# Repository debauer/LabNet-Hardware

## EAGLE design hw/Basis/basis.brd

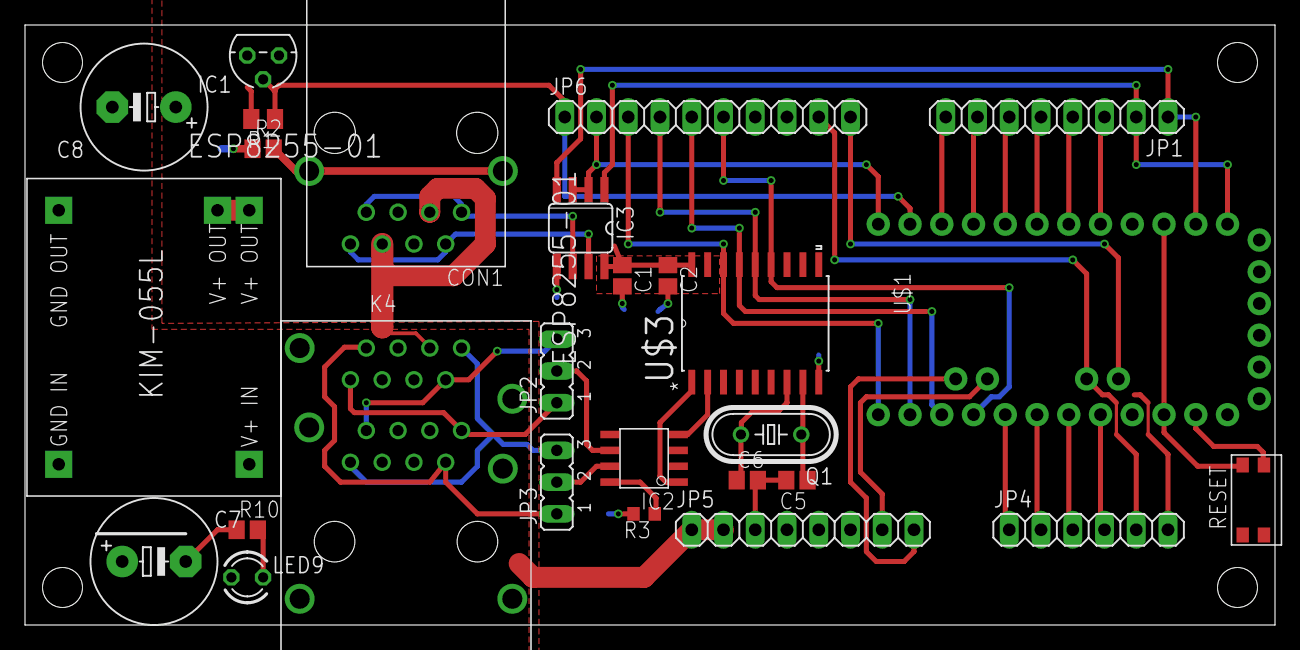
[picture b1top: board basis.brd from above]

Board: 2 copper layers, 100.0 x 48.0 mm, 27 parts (0 on the bottom side), 41 nets.

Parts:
C1, C2, C5, C6: C0805
C7, C8: E5-10,5
CON1: MEBP
IC1: DS1820TO92; TO-92
IC2: MCP2551; SO-8
IC3: MAX481CSA; SO08
JP1, JP5: 1X08
JP2, JP3: JP2
JP4: 1X06
JP6: 1X10
K4: 615016240521
LED9: LED3MM
MOD1: KIM-055L
Q1: HC49/S
R1: M0805
R2, R10: R0805
R3: 10k; R0603
RESET: 434351045816
U$1: ARDUINO_PRO_MINI
U$3: MCP2515-I/SO; SOIC127P1034X264-18N

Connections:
A0: JP4.1, U$1.17
A1: JP4.2, U$1.18
A2: JP4.3, U$1.19
A3_V24: JP4.4, U$1.20
A4_SDA: JP4.5, JP6.9, U$1.A4
A5_SCL: JP6.10, U$1.A5
A6: JP5.8, U$1.A6
A7: JP5.7, U$1.A7
CANH: IC2.7, JP3.2
CANH1: JP3.3, K4.A1, K4.B1
CANH2: JP3.1, K4.A7, K4.B7
CANL: IC2.6, JP2.2
CANL1: JP2.3, K4.A2, K4.B2
CANL2: JP2.1, K4.A8, K4.B8
CANRX: IC2.4, U$3.2
CANTX: IC2.1, U$3.1
D2: JP1.3, U$1.5
D3: JP1.4, U$1.6
D4: JP1.5, U$1.7
D5: JP1.6, U$1.8
D6: JP1.7, U$1.9
D7: JP1.8, U$1.10
D8: IC1.2, JP6.1, R1.1, U$1.11
D9: IC3.2, IC3.3, JP6.2, U$1.12
D10_SS: JP6.3, U$1.13, U$3.16
D11_MOSI: JP6.4, U$1.14, U$3.14
D12_MISO: JP6.5, U$1.15, U$3.15
D13_SCK: JP6.6, U$1.16, U$3.13
GND: C1.2, C2.2, C5.2, C6.2, C7.-, C8.-, CON1.4, CON1.5, IC1.1, IC3.5, JP5.3, JP5.4, JP6.7, K4.A4, K4.A5, K4.B4, K4.B5, MOD1.GNDIN, MOD1.GNDOUT, R2.1, R3.2, R10.1, RESET.2, U$1.4, U$1.23, U$3.9
MCP_OSC1: C5.1, Q1.1, U$3.8
MCP_OSC2: C6.1, Q1.2, U$3.7
unnamed: IC2.8, R3.1
unnamed: CON1.T1, CON1.T2, R2.2
unnamed: LED9.K, R10.2
P5V: C1.1, C2.1, C8.+, IC1.3, IC3.8, JP5.5, JP5.6, MOD1.V+OUT1, MOD1.V+OUT2, R1.2, U$1.21, U$3.18
P24P: C7.+, CON1.3, CON1.6, JP5.1, JP5.2, K4.A3, K4.A6, K4.B3, K4.B6, LED9.A, MOD1.V+IN
RESET: RESET.1, U$1.3, U$1.22
RS485_A: CON1.1, CON1.7, IC3.6
RS485_B: CON1.2, CON1.8, IC3.7
RX: IC3.4, JP1.1, U$1.2
TX: IC3.1, JP1.2, U$1.1

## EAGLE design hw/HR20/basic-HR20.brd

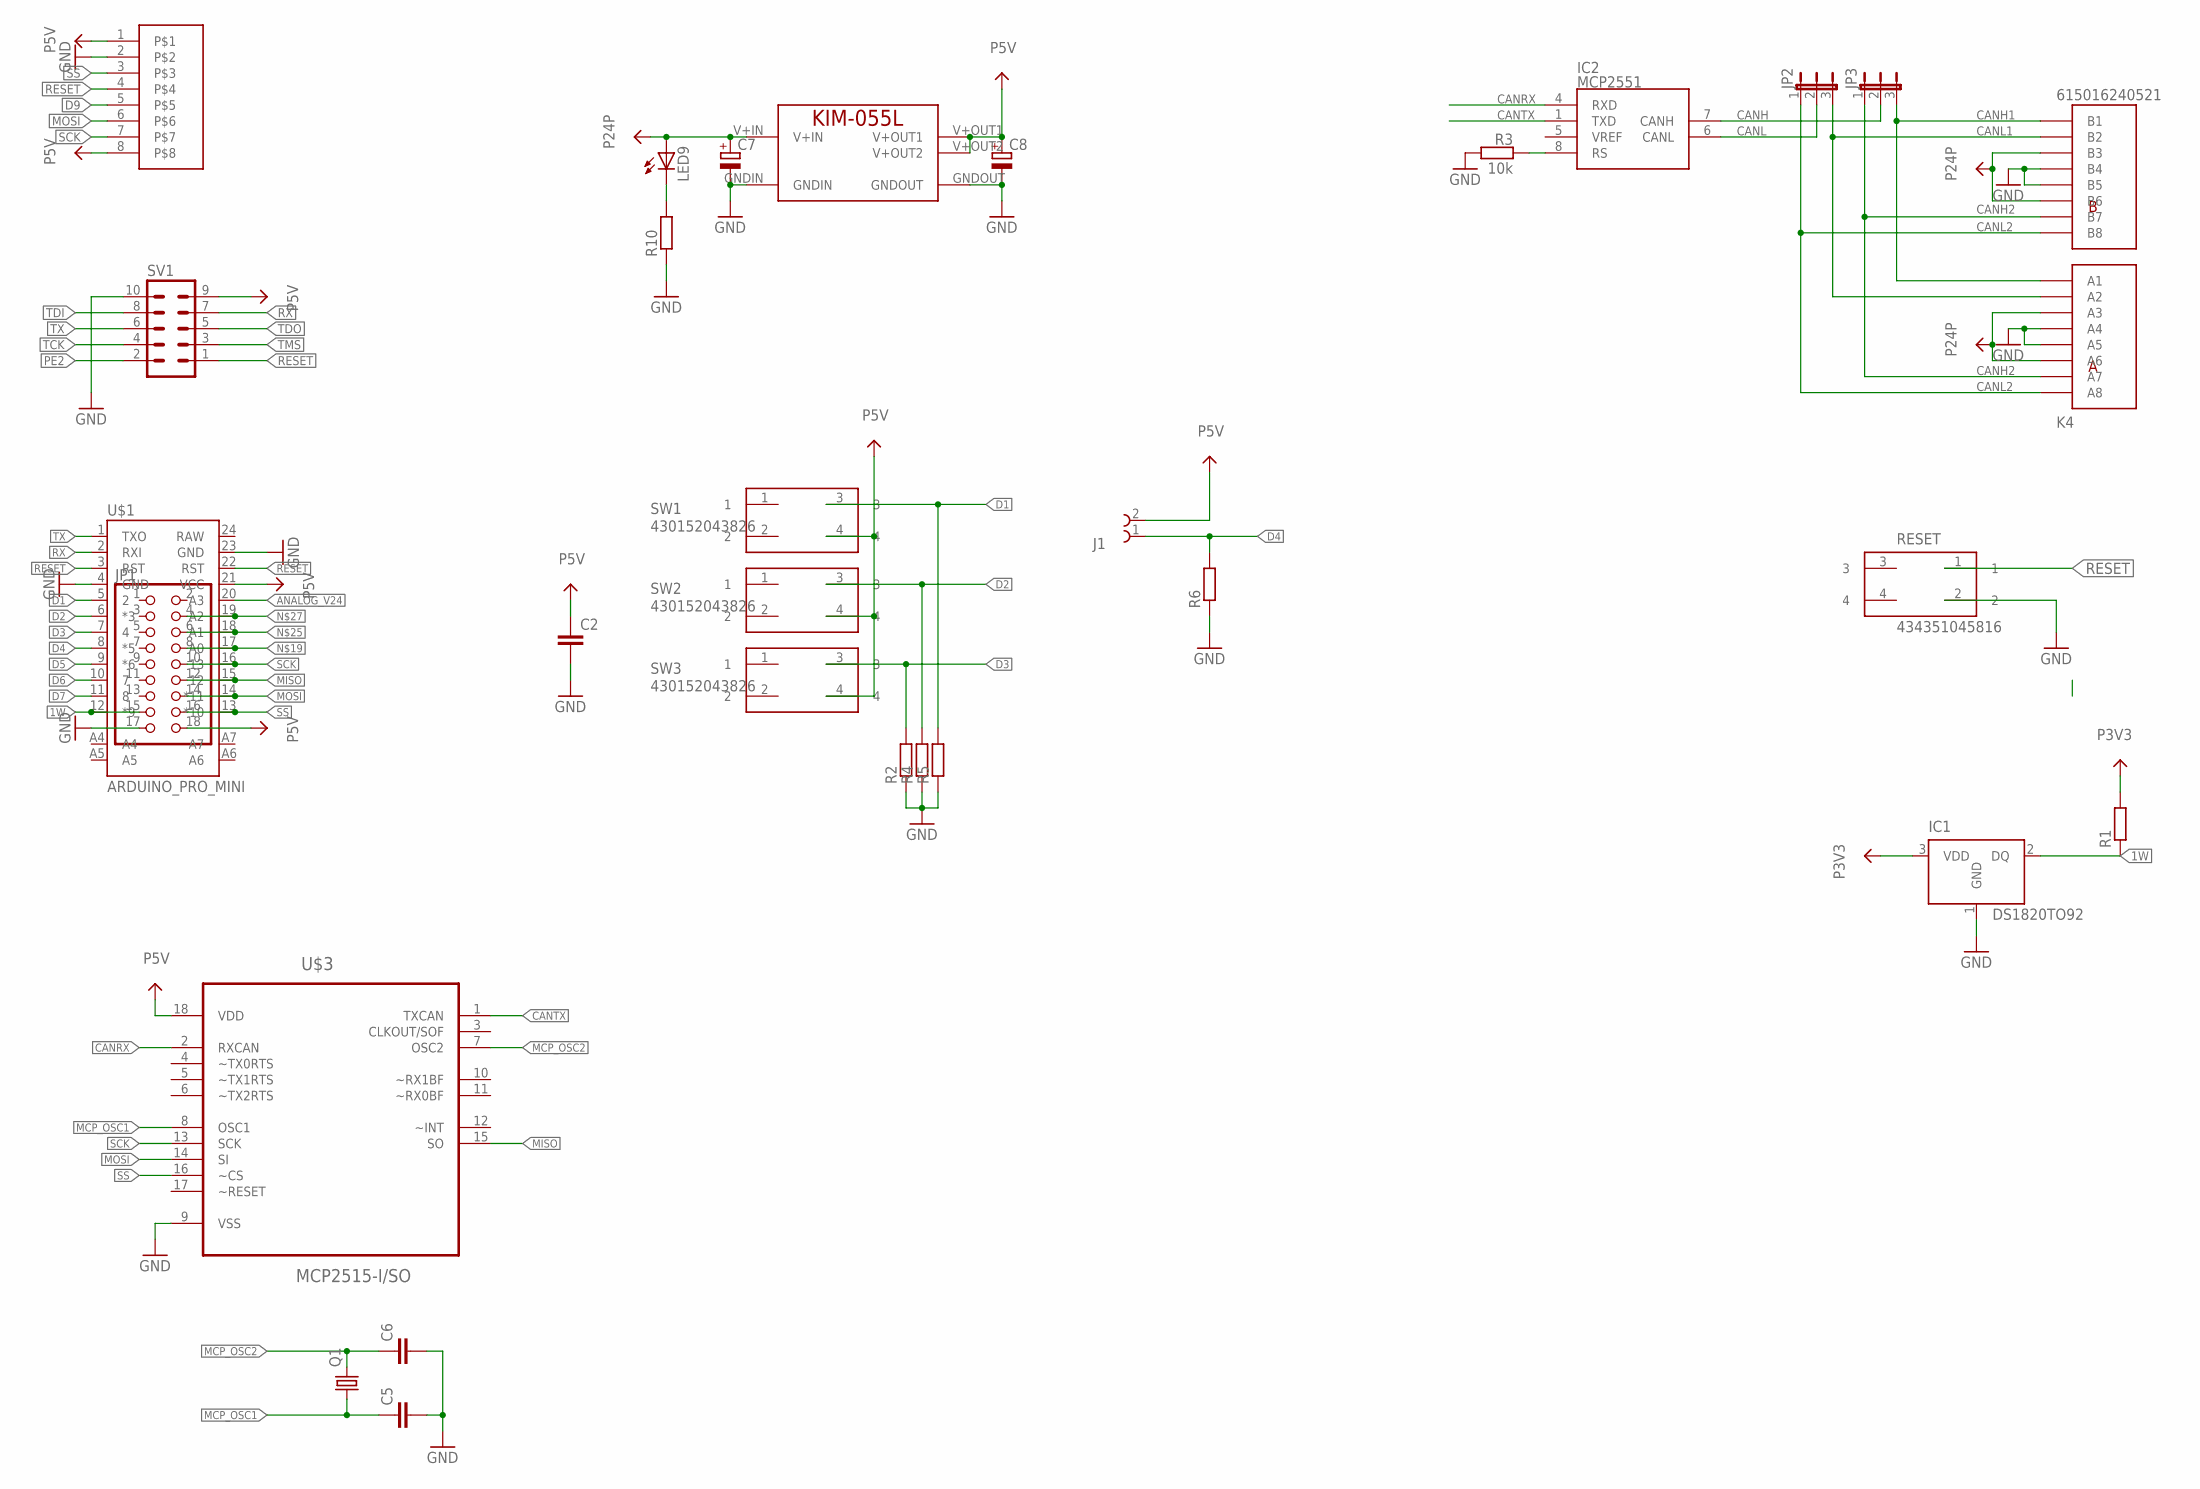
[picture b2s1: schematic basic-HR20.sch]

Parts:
C2, C5, C6: C-EUC0805; C0805
C7, C8: CPOL-EUE5-10.5; E5-10,5
IC1: DS1820TO92; TO-92
IC2: MCP2551; SO-8
J1: 691312510002
JP1: PINHD-2X9; 2X09
JP2, JP3: JP2E; JP2
K4: 615016240521
LED9: LED3MM
MOD1: KIM-055L
Q1: CRYSTALHC49S; HC49/S
R1: R-EU_M0805; M0805
R2, R4, R5, R6, R10: R-EU_R0805; R0805
R3: 10k; R0603
RESET: 434351045816
SV1: ML10
SW1, SW2, SW3: 430152043826
U$1: ARDUINO_PRO_MINI
U$2: 1.44-128X128
U$3: MCP2515-I/SO; SOIC127P1034X264-18N

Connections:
1W: IC1.2 (DQ), JP1.15, R1.1, U$1.12 (*9)
ANALOG_V24: U$1.20 (A3)
CANH: IC2.7 (CANH), JP3.2
CANH1: JP3.3, K4.A1, K4.B1
CANH2: JP3.1, K4.A7, K4.B7
CANL: IC2.6 (CANL), JP2.2
CANL1: JP2.3, K4.A2, K4.B2
CANL2: JP2.1, K4.A8, K4.B8
CANRX: IC2.4 (RXD), U$3.2 (RXCAN)
CANTX: IC2.1 (TXD), U$3.1 (TXCAN)
D1: R5.2, SW1.3, U$1.5 (2)
D2: R4.2, SW2.3, U$1.6 (*3)
D3: R2.2, SW3.3, U$1.7 (4)
D4: J1.1, R6.2, U$1.8 (*5)
D5: U$1.9 (*6)
D6: U$1.10 (7)
D7: U$1.11 (8)
D9: U$2.5
GND: C2.2, C5.2, C6.2, C7.-, C8.-, IC1.1 (GND), JP1.17, K4.A4, K4.A5, K4.B4, K4.B5, MOD1.GNDIN, MOD1.GNDOUT, R2.1, R3.2, R4.1, R5.1, R6.1, R10.1, RESET.2, SV1.10, U$1.4 (GND), U$1.23 (GND), U$2.2, U$3.9 (VSS)
MCP_OSC1: C5.1, Q1.1, U$3.8 (OSC1)
MCP_OSC2: C6.1, Q1.2, U$3.7 (OSC2)
MISO: JP1.12, U$1.15 (12), U$3.15 (SO)
MOSI: JP1.14, U$1.14 (*11), U$2.6, U$3.14 (SI)
unnamed: IC2.8 (RS), R3.1
unnamed: LED9.K (C), R10.2
unnamed: JP1.8, U$1.17 (A0)
unnamed: JP1.6, U$1.18 (A1)
unnamed: JP1.4, U$1.19 (A2)
P3V3: IC1.3 (VDD), R1.2
P5V: C2.1, C8.+, J1.2, JP1.18, MOD1.V+OUT1, MOD1.V+OUT2, SV1.9, SW1.4, SW2.4, SW3.4, U$1.21 (VCC), U$2.1, U$2.8, U$3.18 (VDD)
P24P: C7.+, K4.A3, K4.A6, K4.B3, K4.B6, LED9.A, MOD1.V+IN
PE2: SV1.2
RESET: RESET.1, SV1.1, U$1.3 (RST), U$1.22 (RST), U$2.4
RX: SV1.7, U$1.2 (RXI)
SCK: JP1.10, U$1.16 (13), U$2.7, U$3.13 (SCK)
SS: JP1.16, U$1.13 (*10), U$2.3, U$3.16 (~CS)
TCK: SV1.4
TDI: SV1.8
TDO: SV1.5
TMS: SV1.3
TX: SV1.6, U$1.1 (TXO)

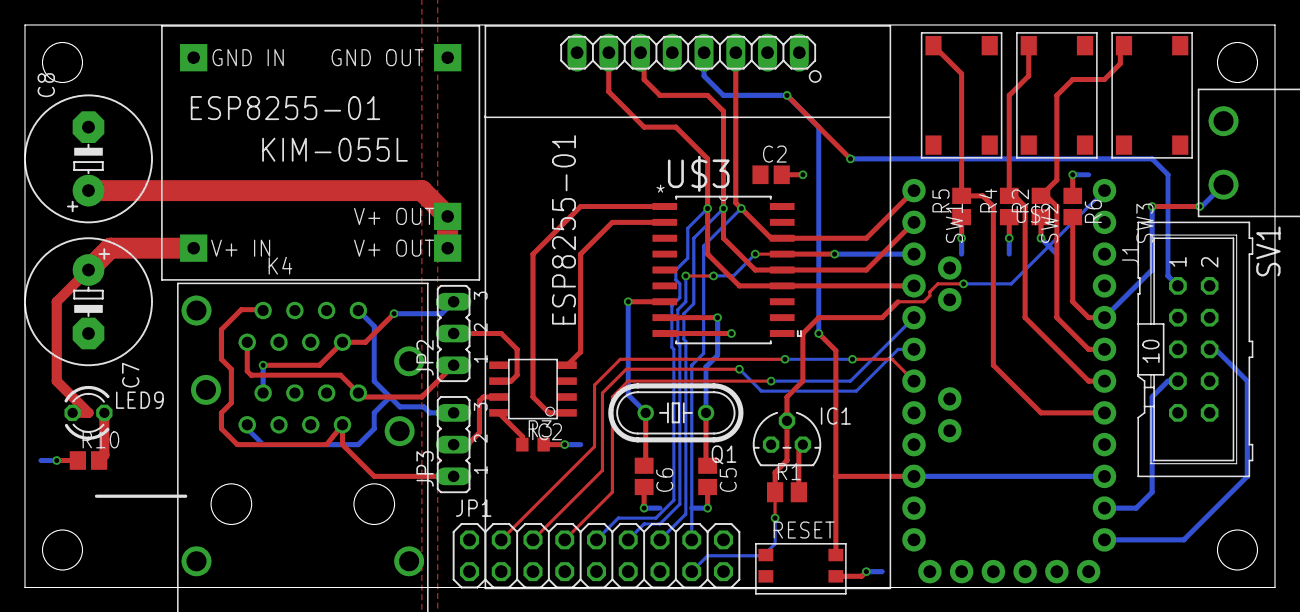
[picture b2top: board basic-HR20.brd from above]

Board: 2 copper layers, 100.0 x 45.0 mm, 30 parts (0 on the bottom side), 31 nets.

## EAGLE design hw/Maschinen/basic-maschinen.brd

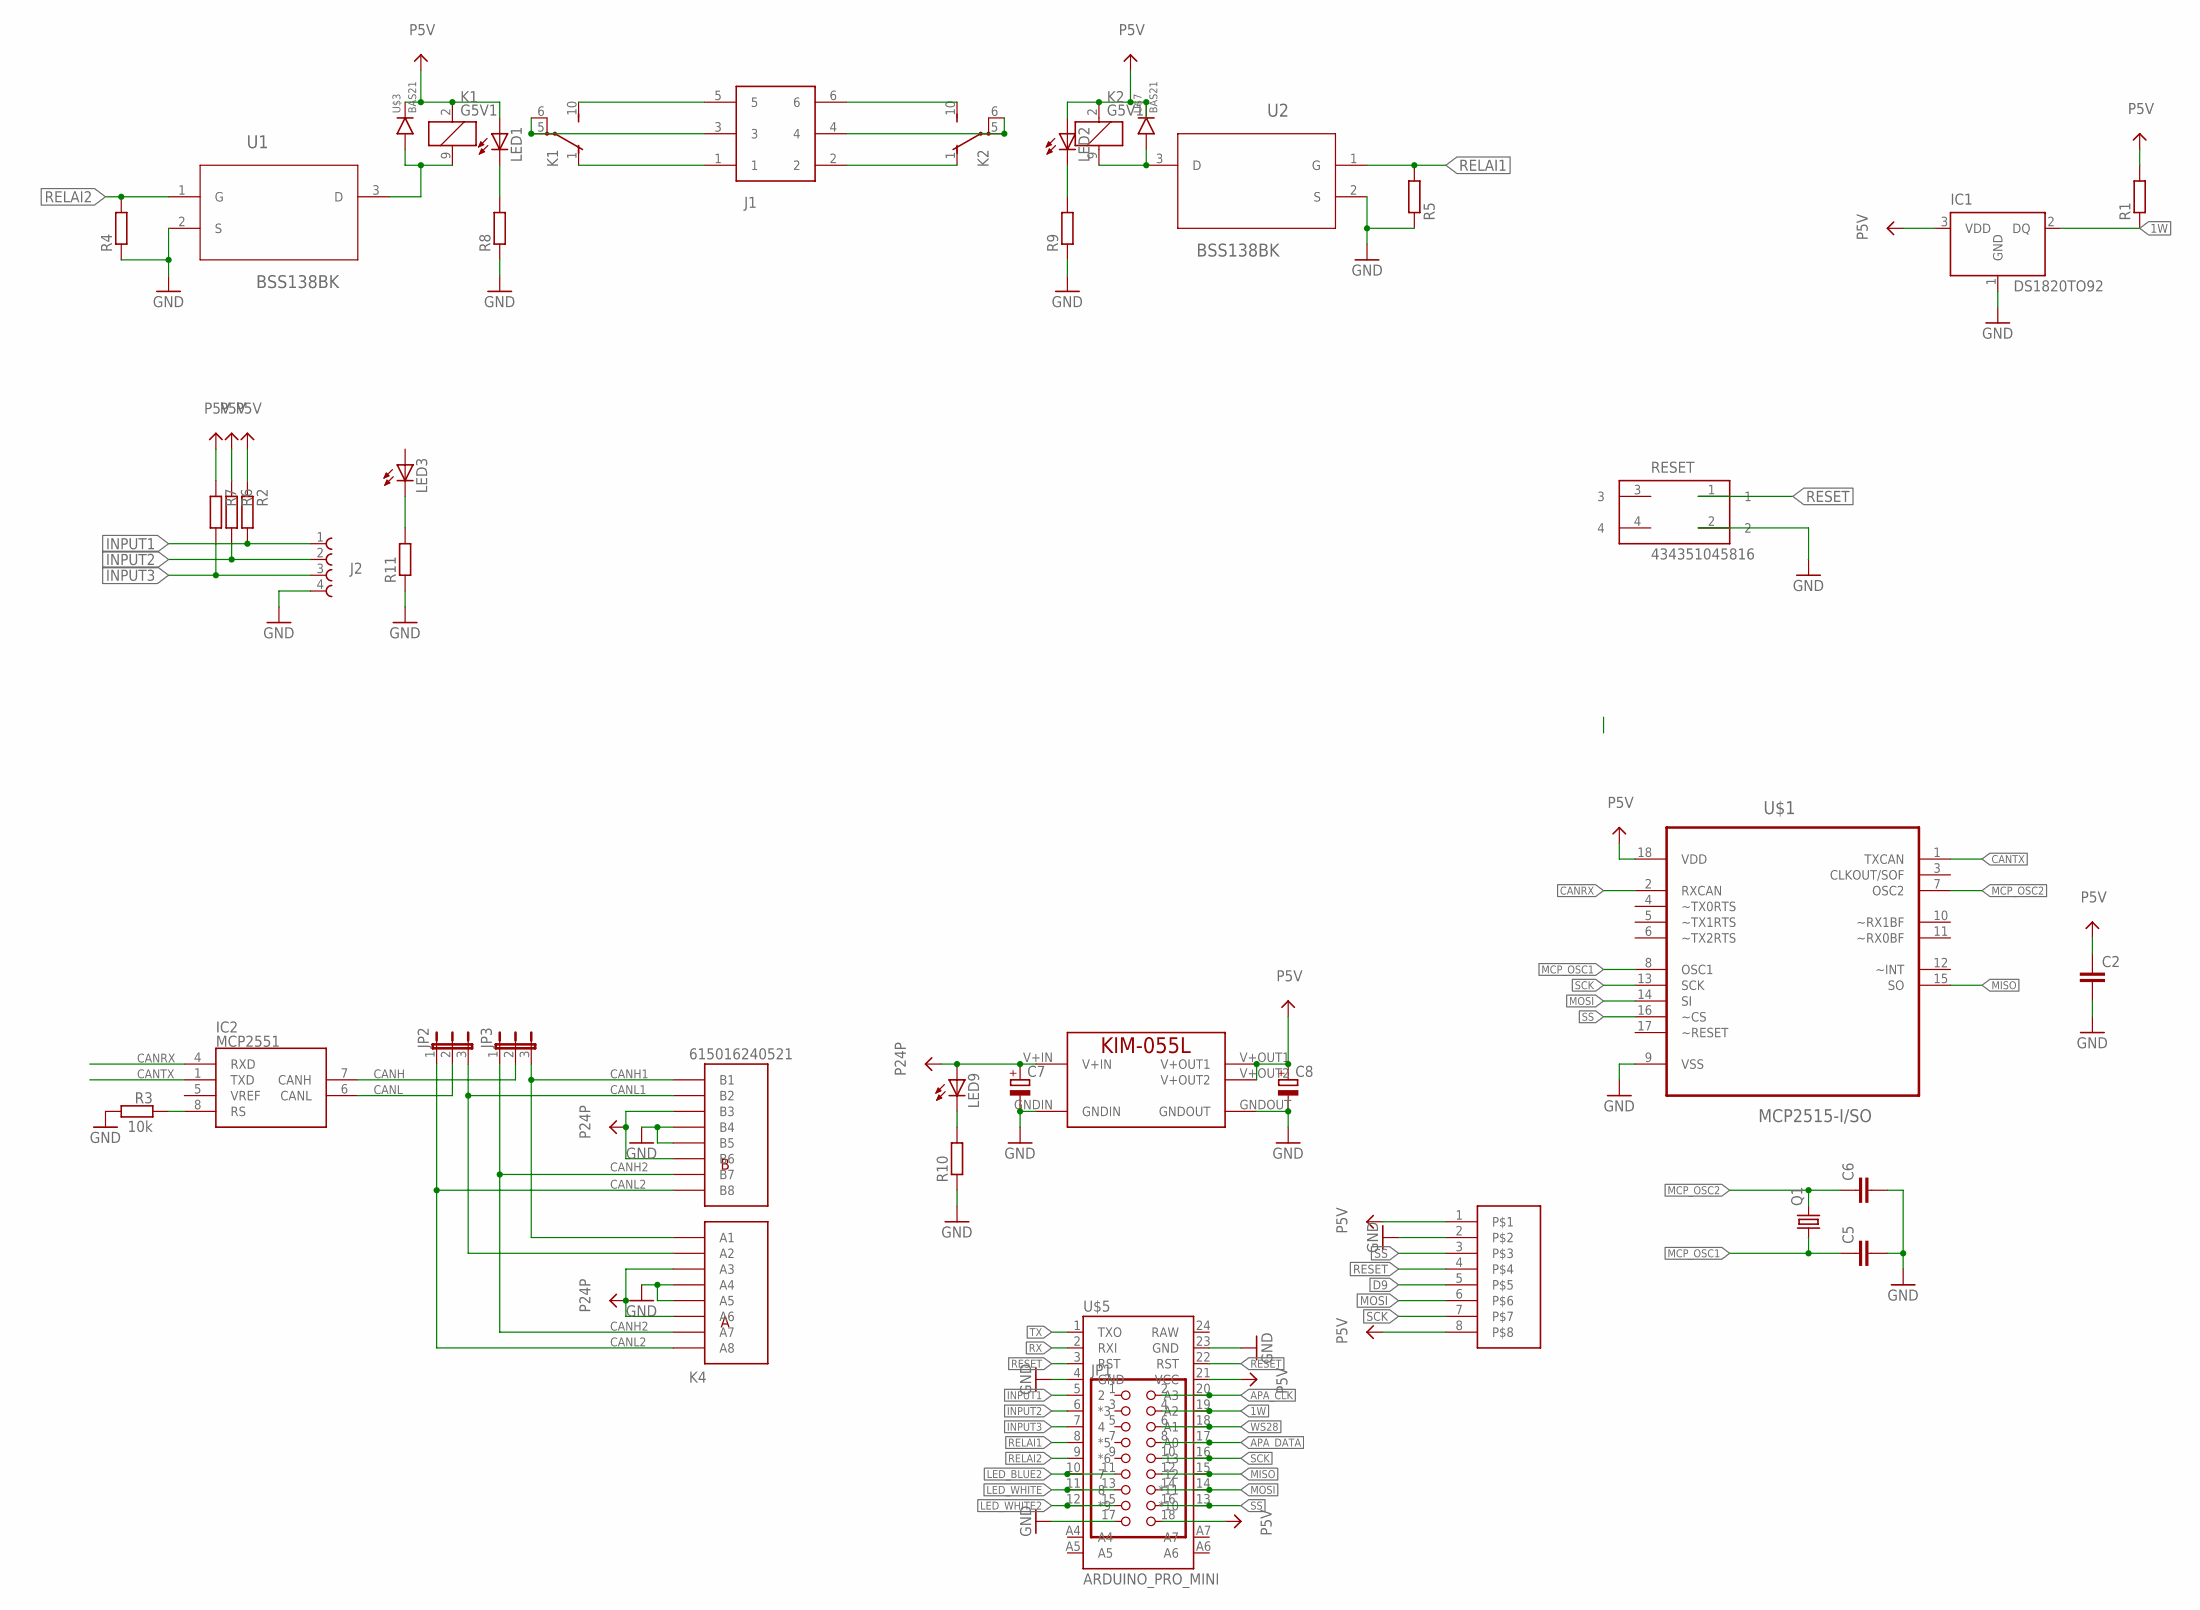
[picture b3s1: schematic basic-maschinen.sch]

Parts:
C2, C5, C6: C-EUC0805; C0805
C7, C8: CPOL-EUE5-10.5; E5-10,5
IC1: DS1820TO92; TO-92
IC2: MCP2551; SO-8
J1: 691327310006
J2: 691322310004
JP1: PINHD-2X9; 2X09
JP2, JP3: JP2E; JP2
K1, K2: G5V1
K4: 615016240521
LED1, LED2, LED3, LED9: LED3MM
MOD1: KIM-055L
Q1: CRYSTALHC49S; HC49/S
R1, R2, R4, R5, R6, R7: R-EU_M0805; M0805
R3: 10k; R0603
R8, R9, R10, R11: R-EU_R0805; R0805
RESET: 434351045816
U1, U2: BSS138BK; SOT65P210X110-3N
U$1: MCP2515-I/SO; SOIC127P1034X264-18N
U$3, U$7: BAS21; SOT23
U$4: 1.44-128X128
U$5: ARDUINO_PRO_MINI

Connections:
1W: IC1.2 (DQ), JP1.4, R1.1, U$5.19 (A2)
APA_CLK: JP1.2, U$5.20 (A3)
APA_DATA: JP1.8, U$5.17 (A0)
CANH: IC2.7 (CANH), JP3.2
CANH1: JP3.3, K4.A1, K4.B1
CANH2: JP3.1, K4.A7, K4.B7
CANL: IC2.6 (CANL), JP2.2
CANL1: JP2.3, K4.A2, K4.B2
CANL2: JP2.1, K4.A8, K4.B8
CANRX: IC2.4 (RXD), U$1.2 (RXCAN)
CANTX: IC2.1 (TXD), U$1.1 (TXCAN)
D9: U$4.5
GND: C2.2, C5.2, C6.2, C7.-, C8.-, IC1.1 (GND), J2.4, JP1.17, K4.A4, K4.A5, K4.B4, K4.B5, MOD1.GNDIN, MOD1.GNDOUT, R3.2, R4.1, R5.1, R8.1, R9.1, R10.1, R11.1, RESET.2, U1.2 (S), U2.2 (S), U$1.9 (VSS), U$4.2, U$5.4 (GND), U$5.23 (GND)
INPUT1: J2.1, R2.2, U$5.5 (2)
INPUT2: J2.2, R6.2, U$5.6 (*3)
INPUT3: J2.3, R7.2, U$5.7 (4)
LED_BLUE2: JP1.11, U$5.10 (7)
LED_WHITE: JP1.13, U$5.11 (8)
LED_WHITE2: JP1.15, U$5.12 (*9)
MCP_OSC1: C5.1, Q1.1, U$1.8 (OSC1)
MCP_OSC2: C6.1, Q1.2, U$1.7 (OSC2)
MISO: JP1.12, U$1.15 (SO), U$5.15 (12)
MOSI: JP1.14, U$1.14 (SI), U$4.6, U$5.14 (*11)
unnamed: J1.6, K2.10 (S)
unnamed: J1.2, K2.1 (O)
unnamed: J1.4, K2.5, K2.6
unnamed: J1.3, K1.5, K1.6
unnamed: J1.5, K1.10 (S)
unnamed: J1.1, K1.1 (O)
unnamed: IC2.8 (RS), R3.1
unnamed: K1.9 (2), U1.3 (D), U$3.1 (A)
unnamed: LED9.K (C), R10.2
unnamed: LED1.K (C), R8.2
unnamed: LED2.K (C), R9.2
unnamed: K2.9 (2), U2.3 (D), U$7.1 (A)
unnamed: LED3.K (C), R11.2
P5V: C2.1, C8.+, IC1.3 (VDD), JP1.18, K1.2 (1), K2.2 (1), LED1.A, LED2.A, MOD1.V+OUT1, MOD1.V+OUT2, R1.2, R2.1, R6.1, R7.1, U$1.18 (VDD), U$3.3 (C), U$4.1, U$4.8, U$5.21 (VCC), U$7.3 (C)
P24P: C7.+, K4.A3, K4.A6, K4.B3, K4.B6, LED9.A, MOD1.V+IN
RELAI1: R5.2, U2.1 (G), U$5.8 (*5)
RELAI2: R4.2, U1.1 (G), U$5.9 (*6)
RESET: RESET.1, U$4.4, U$5.3 (RST), U$5.22 (RST)
RX: U$5.2 (RXI)
SCK: JP1.10, U$1.13 (SCK), U$4.7, U$5.16 (13)
SS: JP1.16, U$1.16 (~CS), U$4.3, U$5.13 (*10)
TX: U$5.1 (TXO)
WS28: JP1.6, U$5.18 (A1)

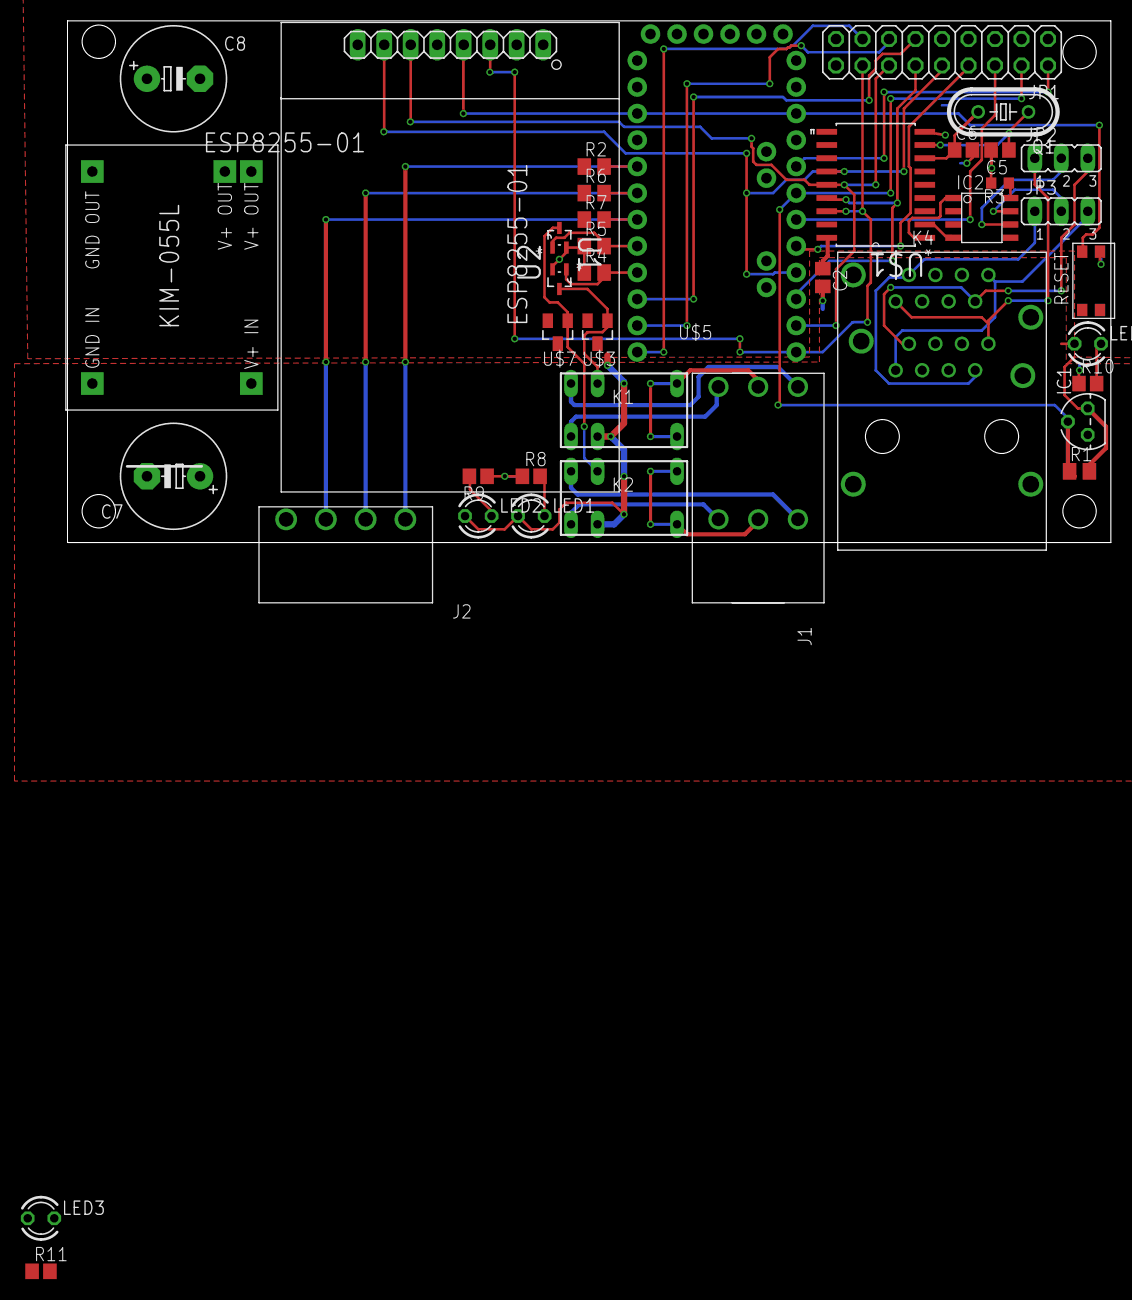
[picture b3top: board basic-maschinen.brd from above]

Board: 2 copper layers, 100.0 x 50.0 mm, 40 parts (0 on the bottom side), 43 nets.

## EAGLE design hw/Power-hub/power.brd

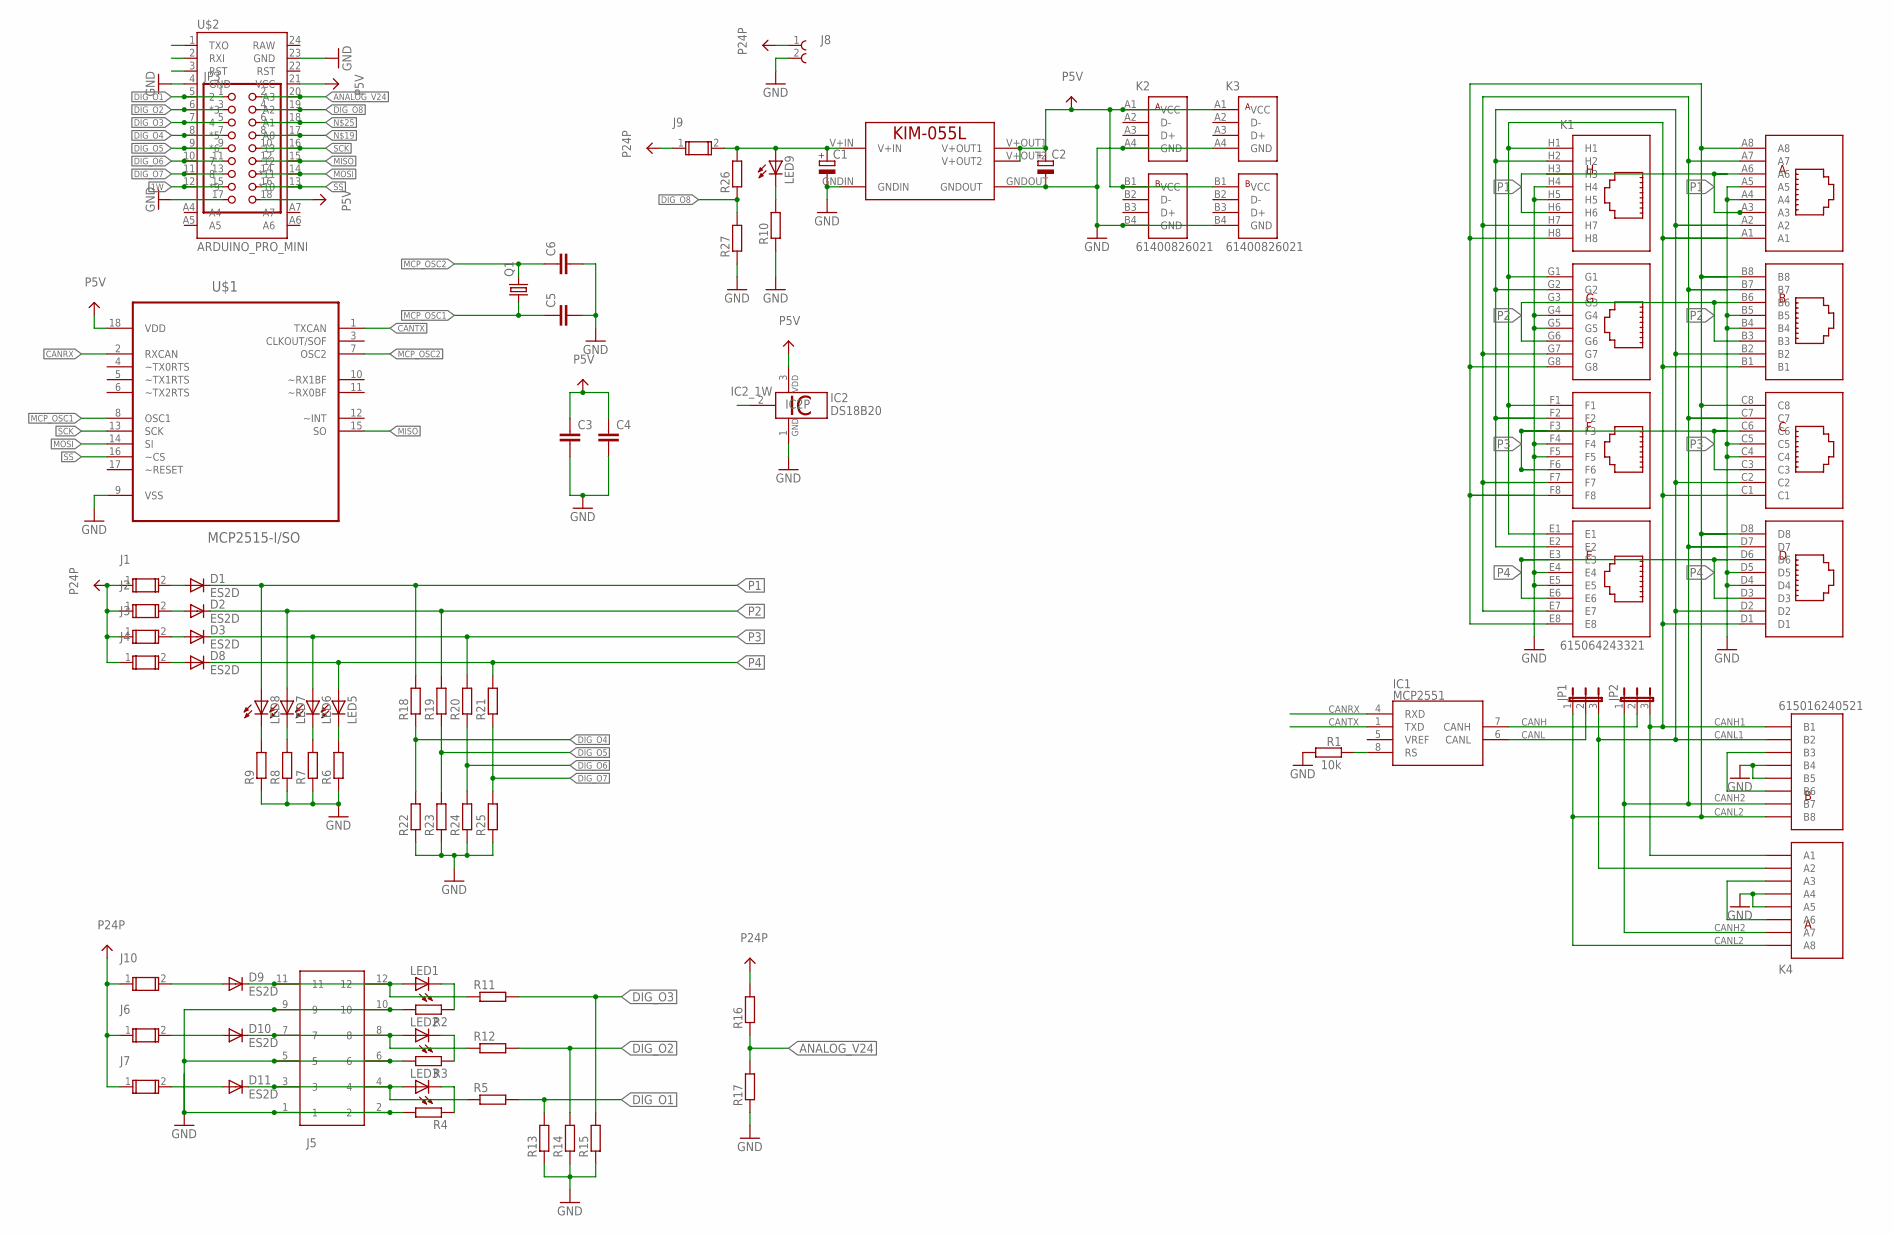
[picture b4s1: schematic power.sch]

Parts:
C1, C2: CPOL-EUE5-10.5; E5-10,5
C3, C4, C5, C6: C-EUC0805; C0805
D1, D2, D3, D8, D9, D10, D11: ES2D; SMB
IC1: MCP2551; SO-8
IC2: DS18B20; TO92-
J1, J2, J3, J4, J6, J7, J9, J10: 696101000002
J5: 691332510012
J8: 691312510002
JP1, JP2: JP2E; JP2
JP3: PINHD-2X9; 2X09
K1: 615064243321
K2, K3: 61400826021
K4: 615016240521
LED1, LED2, LED3, LED5, LED6, LED7, LED8, LED9: LED3MM
MOD1: KIM-055L
Q1: CRYSTALHC49S; HC49/S
R1: 10k; R0603
R2, R3, R4, R5, R6, R7, R8, R9, R10, R11, R12, R13, R14, R15, R16, R17, R18, R19, R20, R21, R22, R23, R24, R25, R26, R27: R-EU_R0805; R0805
U$1: MCP2515-I/SO; SOIC127P1034X264-18N
U$2: ARDUINO_PRO_MINI

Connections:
A0: JP3.8, U$2.17 (A0); also elsewhere on the board
A1: JP3.6, U$2.18 (A1); also elsewhere on the board
A2: JP3.4, R26.1, R27.2, U$2.19 (A2)
A6: U$2.A6; also elsewhere on the board
A7: U$2.A7; also elsewhere on the board
ANALOG_V24: JP3.2, R16.1, R17.2, U$2.20 (A3)
CANH: IC1.7 (CANH), JP2.2
CANH1: JP2.3, K1.A1, K1.B1, K1.C1, K1.D1, K1.E1, K1.F1, K1.G1, K1.H1, K4.A1, K4.B1
CANH2: JP2.1, K1.A7, K1.B7, K1.C7, K1.D7, K1.E7, K1.F7, K1.G7, K1.H7, K4.A7, K4.B7
CANL: IC1.6 (CANL), JP1.2
CANL1: JP1.3, K1.A2, K1.B2, K1.C2, K1.D2, K1.E2, K1.F2, K1.G2, K1.H2, K4.A2, K4.B2
CANL2: JP1.1, K1.A8, K1.B8, K1.C8, K1.D8, K1.E8, K1.F8, K1.G8, K1.H8, K4.A8, K4.B8
CANRX: IC1.4 (RXD), U$1.2 (RXCAN)
CANTX: IC1.1 (TXD), U$1.1 (TXCAN)
D2: JP3.1, R5.2, R13.2, U$2.5 (2)
D3: JP3.3, R12.2, R14.2, U$2.6 (*3)
D4: JP3.5, R11.2, R15.2, U$2.7 (4)
D5: JP3.7, R18.1, R22.2, U$2.8 (*5)
D6: JP3.9, R19.1, R23.2, U$2.9 (*6)
D7: JP3.11, R20.1, R24.2, U$2.10 (7)
D8: JP3.13, R21.1, R25.2, U$2.11 (8)
D9_1W: IC2.2 (1W), JP3.15, U$2.12 (*9)
GND: C1.-, C2.-, C3.2, C4.2, C5.2, C6.2, IC2.1 (GND), J5.1, J5.2, J5.5, J5.6, J5.9, J5.10, J8.2, JP3.17, K1.A4, K1.A5, K1.B4, K1.B5, K1.C4, K1.C5, K1.D4, K1.D5, K1.E4, K1.E5, K1.F4, K1.F5, K1.G4, K1.G5, K1.H4, K1.H5, K2.A4 (GND), K2.B4 (GND), K3.A4 (GND), K3.B4 (GND), K4.A4, K4.A5, K4.B4, K4.B5, MOD1.GNDIN, MOD1.GNDOUT, R1.2, R2.2, R3.2, R4.2, R6.1, R7.1, R8.1, R9.1, R10.1, R13.1, R14.1, R15.1, R17.1, R22.1, R23.1, R24.1, R25.1, R27.1, U$1.9 (VSS), U$2.4 (GND), U$2.23 (GND); also elsewhere on the board
MCP_OSC1: C5.1, Q1.1, U$1.8 (OSC1)
MCP_OSC2: C6.1, Q1.2, U$1.7 (OSC2)
MISO: JP3.12, U$1.15 (SO), U$2.15 (12)
MOSI: JP3.14, U$1.14 (SI), U$2.14 (*11)
unnamed: IC1.8 (RS), R1.1
unnamed: K4.B3, K4.B6
unnamed: C1.+, J9.2, LED9.A, MOD1.V+IN, R26.2
unnamed: D1.A, J1.2
unnamed: K4.A3, K4.A6
unnamed: D2.A, J2.2
unnamed: LED9.K (C), R10.2
unnamed: D9.A, J10.2
unnamed: D11.A, J7.2
unnamed: D3.A, J3.2
unnamed: LED1.K (C), R2.1
unnamed: LED2.K (C), R3.1
unnamed: LED3.K (C), R4.1
unnamed: LED5.K (C), R6.2
unnamed: LED6.K (C), R7.2
unnamed: D8.A, J4.2
unnamed: LED7.K (C), R8.2
unnamed: LED8.K (C), R9.2
unnamed: D10.A, J6.2
unnamed: D9.C, J5.11, J5.12, LED1.A, R11.1
unnamed: D10.C, J5.7, J5.8, LED2.A, R12.1
unnamed: D11.C, J5.3, J5.4, LED3.A, R5.1
P1: D1.C, K1.A3, K1.A6, K1.H3, K1.H6, LED8.A, R18.2
P2: D2.C, K1.B3, K1.B6, K1.G3, K1.G6, LED7.A, R19.2
P3: D3.C, K1.C3, K1.C6, K1.F3, K1.F6, LED6.A, R20.2
P4: D8.C, K1.D3, K1.D6, K1.E3, K1.E6, LED5.A, R21.2
P5V: C2.+, C3.1, C4.1, IC2.3 (VDD), JP3.18, K2.A1 (VCC), K2.B1 (VCC), K3.A1 (VCC), K3.B1 (VCC), MOD1.V+OUT1, MOD1.V+OUT2, U$1.18 (VDD), U$2.21 (VCC); also elsewhere on the board
P24P: J1.1, J2.1, J3.1, J4.1, J6.1, J7.1, J8.1, J9.1, J10.1, R16.2; also elsewhere on the board
RX: U$2.2 (RXI); also elsewhere on the board
SCK: JP3.10, U$1.13 (SCK), U$2.16 (13)
SCL: U$2.A5; also elsewhere on the board
SDA: U$2.A4; also elsewhere on the board
SS: JP3.16, U$1.16 (~CS), U$2.13 (*10)
TX: U$2.1 (TXO); also elsewhere on the board

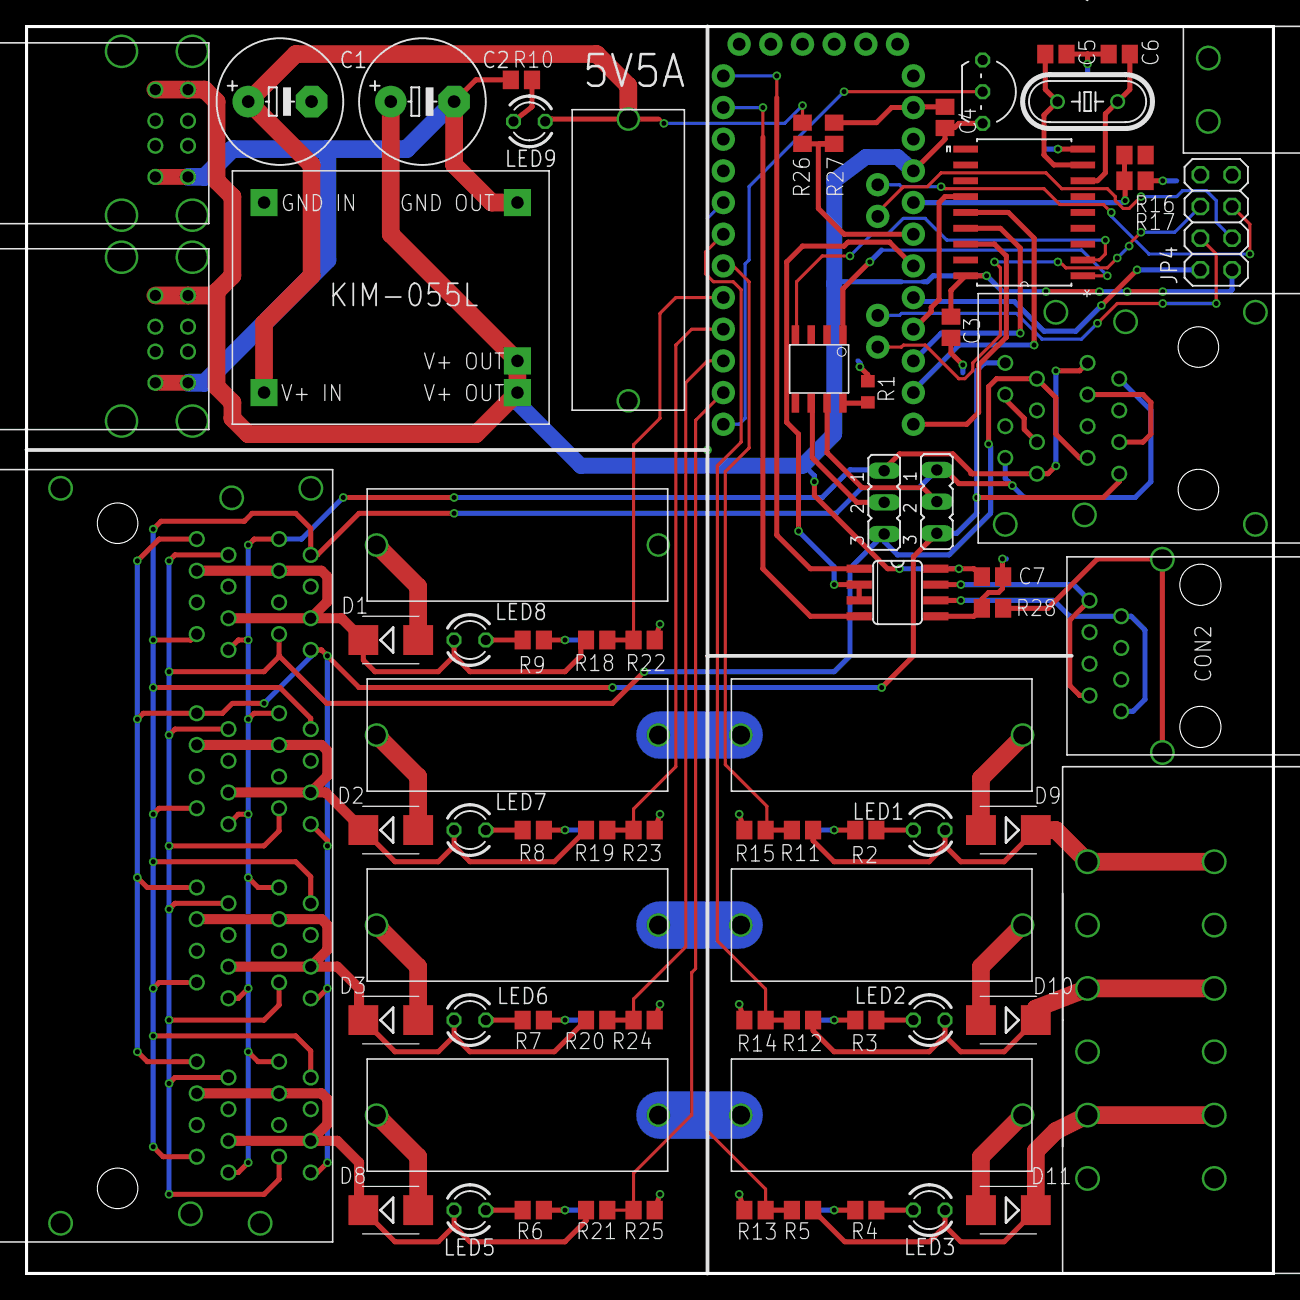
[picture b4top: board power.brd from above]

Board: 2 copper layers, 100.0 x 100.0 mm, 75 parts (0 on the bottom side), 64 nets.

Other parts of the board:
C7: C0805
CON2: MEBP
IC3: MAX481CSA; SO08
JP4: 2X04
R28: R0805

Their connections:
A0: JP4.2; also elsewhere on the board
A1: IC3.2, IC3.3; also elsewhere on the board
A6: JP4.6; also elsewhere on the board
A7: JP4.4; also elsewhere on the board
GND: C7.2, CON2.4, CON2.5, IC3.5, JP4.7, R28.1; also elsewhere on the board
unnamed: CON2.T1, CON2.T2, R28.2
P5V: C7.1, IC3.8, JP4.1; also elsewhere on the board
P24P: CON2.3, CON2.6, JP4.8; also elsewhere on the board
RS485_A: CON2.1, CON2.7, IC3.6
RS485_B: CON2.2, CON2.8, IC3.7
RX: IC3.4; also elsewhere on the board
SCL: JP4.5; also elsewhere on the board
SDA: JP4.3; also elsewhere on the board
TX: IC3.1; also elsewhere on the board

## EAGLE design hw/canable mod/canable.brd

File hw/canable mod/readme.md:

# moved

https://github.com/fablab-ka/LabNet-canable

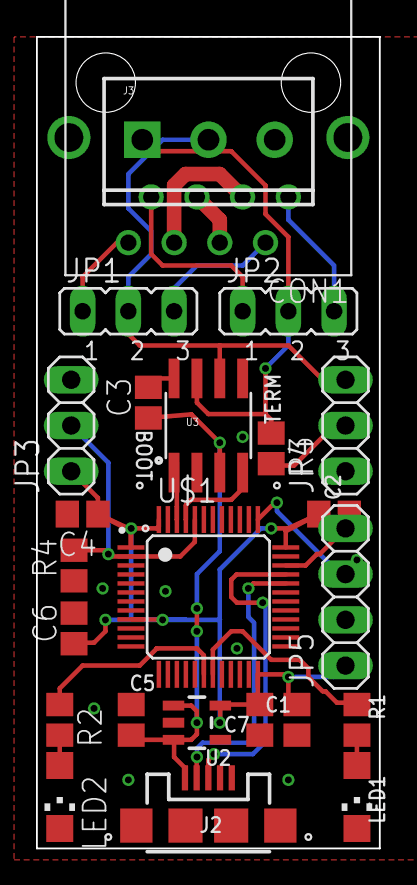
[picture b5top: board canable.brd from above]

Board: 2 copper layers, 19.1 x 45.1 mm, 25 parts (1 on the bottom side), 24 nets.

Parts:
C1, C2, C3, C4, C6: 0.1uF; C0805
C5, C7: 4.7uF; C0805
CON1: MEBP
J2: USB-MICROB
J3: SCREWTERMINAL-3.5MM-3_LOCK.007S
JP1, JP2: JP2
JP3, JP4: 1X03
JP5: 1X04
LED1, LED2: CHIPLED_1206
R1, R2, R4: R0805
R3: 120; R0805
U2: AP2202K-3.3TRG1; SOT23-5
U3: MCP2551; SO08
U$1: STM32F042C6T6; LQFP48
U$2: CANABLE-LOGO

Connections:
3.3V: C1.1, C2.1, C4.1, C6.1, C7.1, JP3.1, JP5.1, U2.5, U$1.1, U$1.9, U$1.24, U$1.36, U$1.48
BOOT0: JP3.2, R4.2, U$1.2, U$1.44
CANH: J3.1, JP2.2, R3.1, U3.7
CANH1: CON1.1, JP2.3
CANH2: CON1.7, JP2.1
CANL: J3.2, JP1.2, JP4.3, U3.6
CANL1: CON1.2, JP1.3
CANL2: CON1.8, JP1.1
CAN_RX: U3.4, U$1.45
CAN_TX: U3.1, U$1.46
D+: J2.D+, U$1.33
D-: J2.D-, U$1.32
FGND: CON1.T1, CON1.T2
GND: C1.2, C2.2, C3.2, C4.2, C5.1, C6.2, C7.2, J2.GND, J2.MT1, J2.MT2, J3.3, JP5.2, LED1.C, LED2.C, R4.1, U2.2, U3.2, U3.8, U$1.8, U$1.23, U$1.35, U$1.47
LED_RX: R1.1, U$1.19
LED_TX: R2.1, U$1.18
unnamed: CON1.3, CON1.6
unnamed: LED2.A, R2.2
unnamed: JP4.2, R3.2
unnamed: CON1.4, CON1.5
unnamed: LED1.A, R1.2
SWCLK: JP5.3, U$1.37
SWDIO: JP5.4, U$1.34
V_BATT: C3.1, C5.2, J2.VBUS, U2.1, U2.3, U3.3

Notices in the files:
parts and their libraries:
Illuminated_Switches: Copyright: Würth Elektronik
SparkFun-Boards: Licensing: Creative Commons ShareAlike 4.0 International - https://creativecommons.org/licenses/by-sa/4.0
